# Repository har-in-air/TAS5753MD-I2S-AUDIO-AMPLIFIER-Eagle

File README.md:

# TAS5753MD-I2S-AUDIO-AMPLIFIER-Eagle
Digital audio power amplifier with I2S interface using TI's TAS5753MD chip

Eagle schematic, layout and gerber files

Uses Stereo Bridge Tied Load application schematic from the TI datasheet. Added an A04409 PMOSFET and BSS138 NMOSFET to allow controlled PVDD on/off. Added MAX16904 3.3V (max 600mA) switching regulator to power the TTL logic 3.3V supply - this can also be used to supply 3.3V to the driving circuit, e.g. Espressif ESP32 module with web radio or bluetooth speaker firmware.

Features : 
1. PVDD range is 4.5V to 24V
2. Can drive 4ohm speakers
3. 90% efficiency
4. 0.2%THD @ 10W rms/channel into 4ohms with PVDD = 12V
5. Requires external MCLK. However, if used with 44.1kHz or 48kHz sampling rates, and the bit clock (BCK / SCLK) is at least 64 x sampling rate, then MCLK can be tied to BCK. A solder jumper is provided for this. This is how I have tested the board.

## Components
See the datasheet for recommendations. The specific packages used in the layout are :

### Capacitors

1206 : C16, C21, C35, C36, C37

0805 : C1, C3, C14

0603 : remaining smt ceramic caps

### Resistors
All are 0603 package. R9 (18K) needs to be 1% precision. Either populate R7 OR R8 to set the LSb of the TAS5753MD I2C slave address. R4 (22K) should be shorted or replaced with a 0 ohm resistor if PVDD is less than 10V, to ensure that the PMOSFET fully turns on.

I found all the passive components on Aliexpress and Ebay. E.g.:

https://www.aliexpress.com/item/10pcs-lot-12-12-7-15UH-SMT-SMD-Patch-Shielding-Power-Inductors-150-Electronic-Components-Free/32591194870.html

https://www.aliexpress.com/item/10pcs-0-68uF-684J-100V-Free-shipping-CBB-Polypropylene-film-capacitor-pitch-5mm-684-100V-680nF/32712243979.html

https://www.aliexpress.com/item/100pcs-lot-100nF-X7R-Error-10-50V-0603-smd-capacitor/32318089455.html

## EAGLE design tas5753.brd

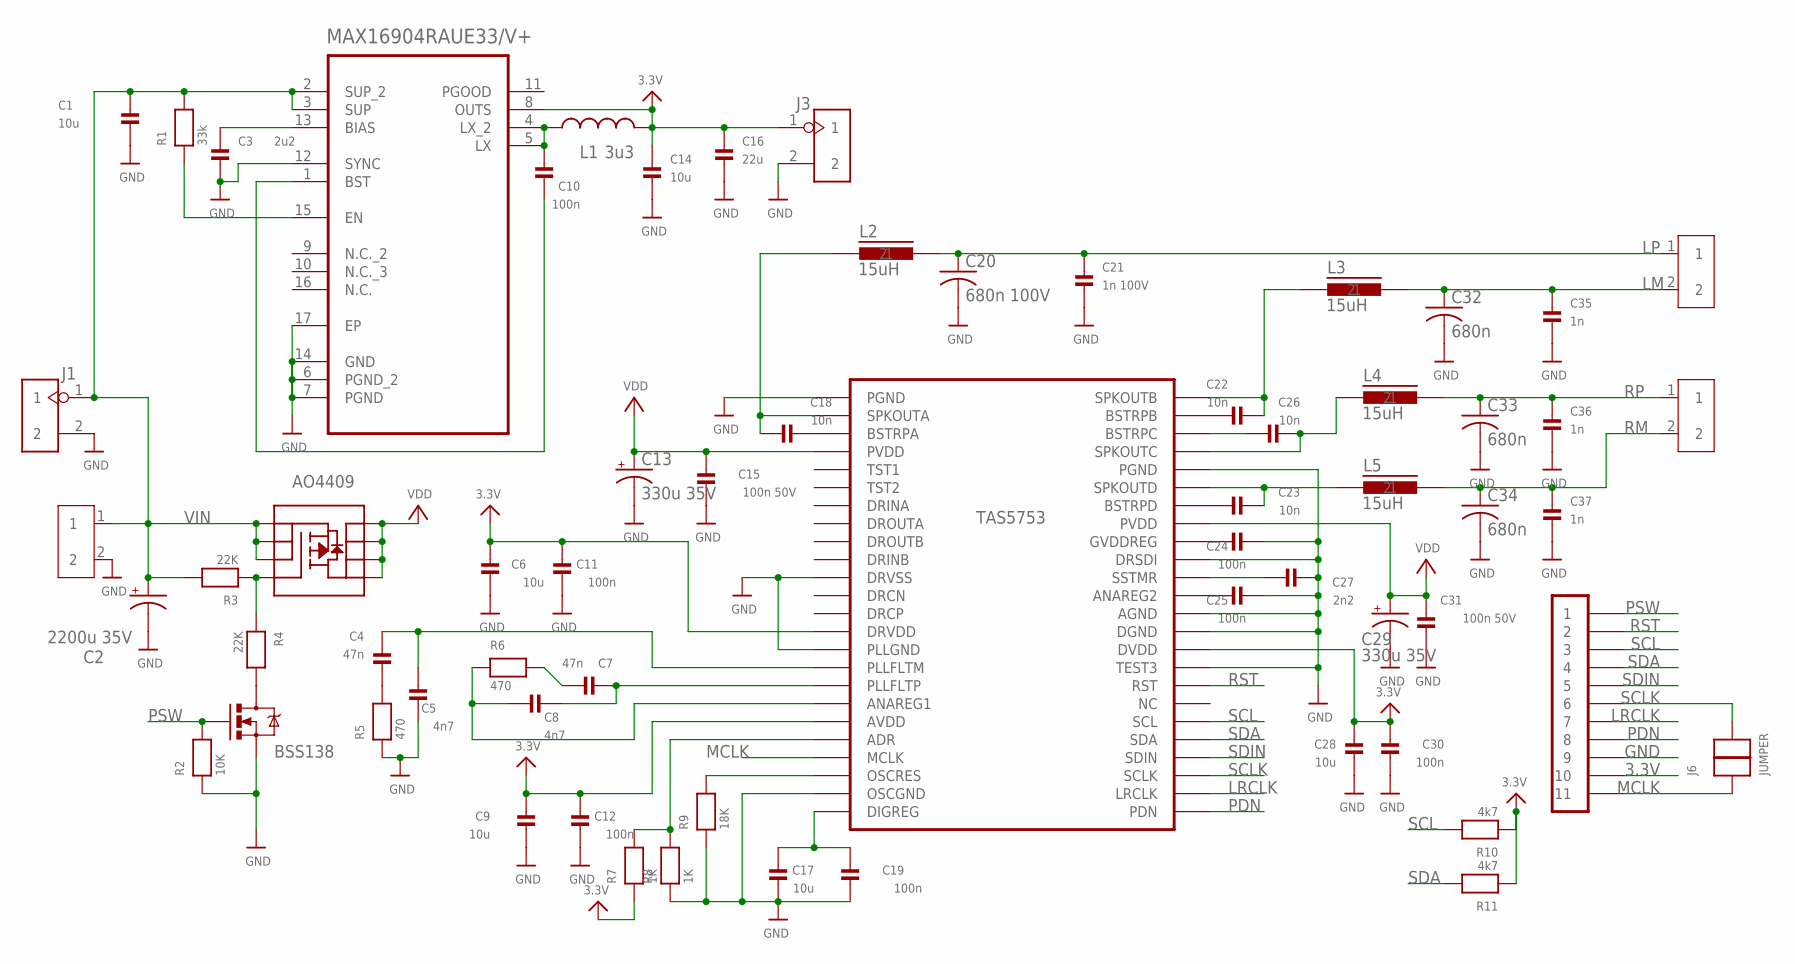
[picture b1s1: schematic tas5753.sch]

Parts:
C1, C14: 10u; 0805
C2: 2200u 35V; CPOL-RADIAL-1000UF-25V
C3: 2u2; 0805
C4, C7: 47n; 0603
C5, C8: 4n7; 0603
C6, C9, C17, C28: 10u; 0603
C10, C11, C12, C19, C24, C25, C30: 100n; 0603
C13, C29: 330u 35V; PANASONIC_E
C15, C31: 100n 50V; 0603
C16: 22u; 1206
C18, C22, C23, C26: 10n; 0603
C20: 680n 100V; C050-045X075
C21: 1n 100V; 1206
C27: 2n2; 0603
C32, C33, C34: 680n; C050-045X075
C35, C36, C37: 1n; 1206
IC1: AO4409; SO08
J1, J3: HEADER-2P-2.0; 2P-2.0
J2, J4, J5: SCREW-TERMINAL-2P'5.08'; 2P-5.08
J6: JUMPER
L1: 3u3; CR54
L2, L3, L4, L5: 15uH; DR125
P1: CONN_1X11_SMT_254; CONN_SMT_1X11_254
Q1: BSS138; SOT23
R1: 33k; 0603
R2: 10K; 0603
R3, R4: 22K; 0603
R5, R6: 470; 0603
R7, R8: 1K; 0603
R9: 18K; 0603
R10, R11: 4k7; 0603
U1: MAX16904RAUE33/V+; SOP65P638X110-17N
U2: TAS5753; HTSSOP_48

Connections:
3.3V: C6.1, C9.1, C11.1, C12.1, C14.1, C16.1, C28.1, C30.1, J3.1, L1.P$2 (2), P1.P$10 (10), R7.1, R10.1, R11.1, U1.8 (OUTS), U2.P$14 (DRVDD), U2.P$19 (AVDD), U2.P$34 (DVDD)
GND: C1.2, C2.2 (-), C3.2, C5.1, C6.2, C9.2, C11.2, C12.2, C13.-, C14.2, C15.1, C16.2, C17.2, C19.2, C20.2, C21.2, C24.2, C25.2, C27.2, C28.2, C29.-, C30.2, C31.1, C32.2, C33.2, C34.2, C35.2, C36.2, C37.2, J1.2, J2.2, J3.2, P1.P$9 (9), Q1.2 (S), R2.1, R5.1, R8.1, R9.1, U1.6 (PGND_2), U1.7 (PGND), U1.12 (SYNC), U1.14 (GND), U1.17 (EP), U2.P$1 (PGND), U2.P$11 (DRVSS), U2.P$15 (PLLGND), U2.P$23 (OSCGND), U2.P$33 (TEST3), U2.P$35 (DGND), U2.P$36 (AGND), U2.P$39 (DRSDI), U2.P$44 (PGND), U2.P$49 (PGND)
LM: C32.1, C35.1, J4.2, L3.2
LP: C20.1, C21.1, J4.1, L2.2
LRCLK: P1.P$7 (7), U2.P$26 (LRCLK)
MCLK: J6.1, P1.P$11 (11), U2.P$21 (MCLK)
unnamed: R9.2, U2.P$22 (OSCRES)
unnamed: C7.2, R6.2
unnamed: C18.2, U2.P$3 (BSTRPA)
unnamed: C7.1, C8.1, U2.P$17 (PLLFLTP)
unnamed: C26.1, U2.P$46 (BSTRPC)
unnamed: C22.1, U2.P$47 (BSTRPB)
unnamed: C22.2, L3.1, U2.P$48 (SPKOUTB)
unnamed: C26.2, L4.1, U2.P$45 (SPKOUTC)
unnamed: R7.2, R8.2, U2.P$20 (ADR)
unnamed: C4.1, R5.2
unnamed: C18.1, L2.1, U2.P$2 (SPKOUTA)
unnamed: C4.2, C5.2, U2.P$16 (PLLFLTM)
unnamed: C23.1, U2.P$42 (BSTRPD)
unnamed: C23.2, L5.1, U2.P$43 (SPKOUTD)
unnamed: C27.1, U2.P$38 (SSTMR)
unnamed: C25.1, U2.P$37 (ANAREG2)
unnamed: IC1.4 (G), R3.1, R4.1
unnamed: C24.1, U2.P$40 (GVDDREG)
unnamed: C10.1, L1.P$1 (1), U1.4 (LX_2), U1.5 (LX)
unnamed: C10.2, U1.1 (BST)
unnamed: C8.2, R6.1, U2.P$18 (ANAREG1)
unnamed: C3.1, U1.13 (BIAS)
unnamed: R1.1, U1.15 (EN)
unnamed: C17.1, C19.1, U2.P$24 (DIGREG)
unnamed: Q1.3 (D), R4.2
PDN: P1.P$8 (8), U2.P$25 (PDN)
PSW: P1.P$1 (1), Q1.1 (G), R2.2
RM: C34.1, C37.1, J5.2, L5.2
RP: C33.1, C36.1, J5.1, L4.2
RST: P1.P$2 (2), U2.P$32 (RST)
SCL: P1.P$3 (3), R10.2, U2.P$30 (SCL)
SCLK: J6.2, P1.P$6 (6), U2.P$27 (SCLK)
SDA: P1.P$4 (4), R11.2, U2.P$29 (SDA)
SDIN: P1.P$5 (5), U2.P$28 (SDIN)
VDD: C13.+, C15.2, C29.+, C31.2, IC1.5 (D), IC1.6 (D), IC1.7 (D), IC1.8 (D), U2.P$4 (PVDD), U2.P$41 (PVDD)
VIN: C1.1, C2.1 (+), IC1.1 (S), IC1.2 (S), IC1.3 (S), J1.1, J2.1, R1.2, R3.2, U1.2 (SUP_2), U1.3 (SUP)

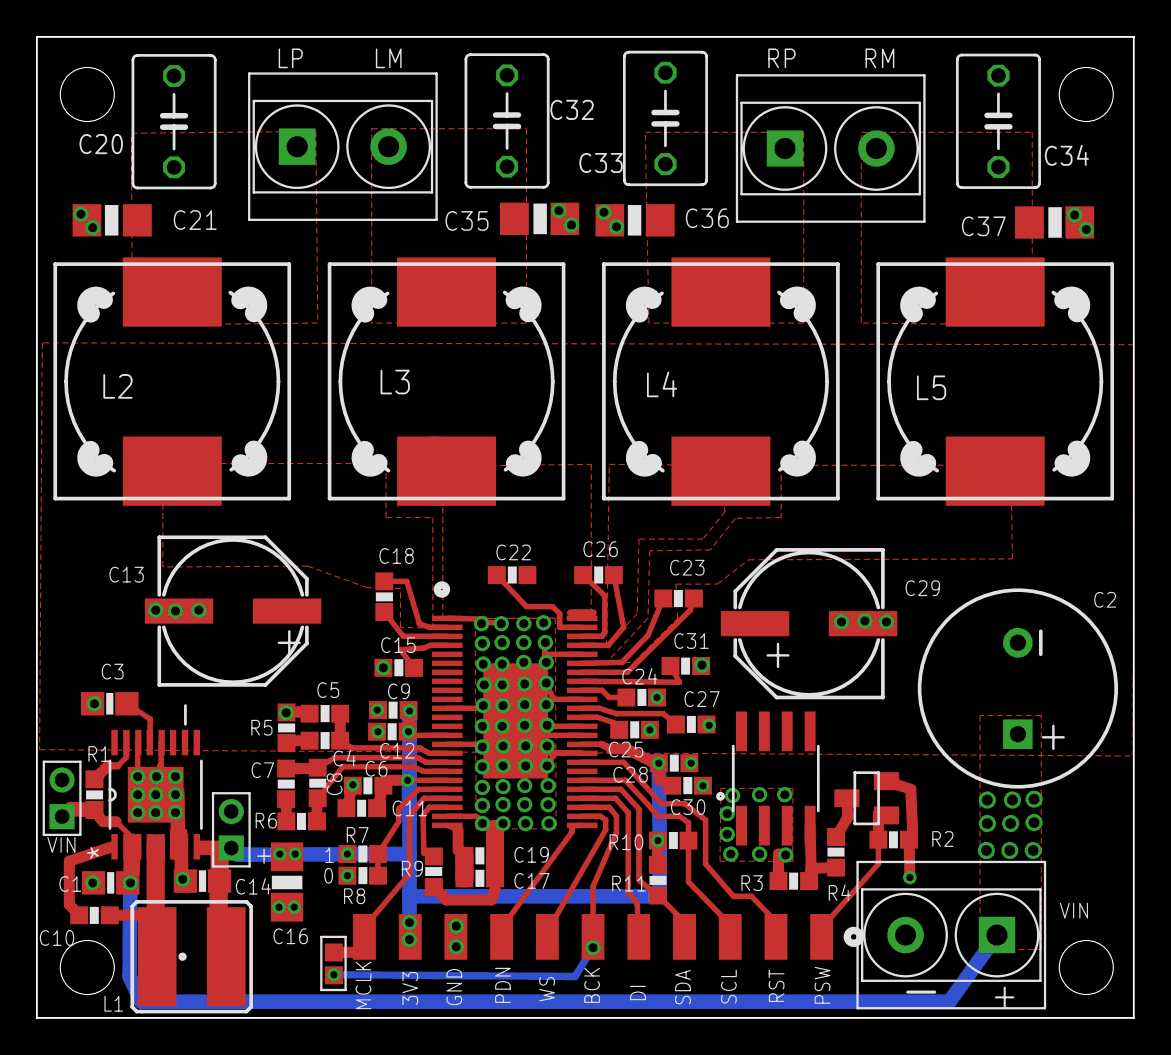
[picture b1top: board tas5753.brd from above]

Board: 2 copper layers, 60.9 x 54.5 mm, 64 parts (0 on the bottom side), 42 nets.

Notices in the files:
parts and their libraries:
SparkFun-Passives: Licensing: Creative Commons ShareAlike 4.0 International - https://creativecommons.org/licenses/by-sa/4.0
microbuilder: This work is placed in the public domain, and may be freely used for commercial and non-commercial work with the following conditions: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
